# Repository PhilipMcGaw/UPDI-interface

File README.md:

# UPDI-interface

This is a KiCad PCB that breaks out a common USB‑to‑TTL serial adapter (often sold as a “USB to TTL Serial Communication Conversion Module”) into UPDI, UART, and RS‑485 interfaces. The board is meant to sit between your USB adapter and targets such I am using it with my ROV project.

## UART TX/RX swapping (poka‑yoke)

Getting UART TX and RX the wrong way round is easy at design time and painful to fix once the board is built. I have implemented a [poka‑yoke](https://en.wikipedia.org/wiki/Poka-yoke) crossover: two solder bridges  let you route either straight‑through or swapped connections by changing which pads are bridged—no trace cuts or bodge wires. How it works and how to use it in other projects: [UART TX/RX swapping made simple](https://philipmcgaw.com/uart-tx-rx-swapping-made-simple/).

## License

 * Hardware design files in this repository are licensed under the **[CERN Open Hardware Licence v2 — Strongly Reciprocal (CERN-OHL-S-2.0)](https://gitlab.com/ohwr/project/cernohl/-/wikis/uploads/819d71bea3458f71fba6cf4fb0f2de6b/cern_ohl_s_v2.txt)**, an open source hardware license recommended by the [Open Source Hardware Association (OSHWA)](https://oshwa.org/).
 * Software files in this repository are licensed under the **[Creatice Commons - Attribution-NonCommercial-ShareAlike 4.0 International (CC BY-NC-SA 4.0)](https://creativecommons.org/licenses/by-nc-sa/4.0/)**

- **Copyright:** [Philip McGaw](https://philipmcgaw.com/)

You may use, study, modify, and redistribute the sorcecode, schematic and PCB layout under those terms. **Derivative designs must be released under the same license(s).** If you share the design or boards built from it, include a link to the licenses.

## Related links

- [SquashedFly](https://squashedfly.eu/)
- [UART TX/RX swapping made simple](https://philipmcgaw.com/uart-tx-rx-swapping-made-simple/) — poka‑yoke UART symbol and footprints used on this board
- [KiCad](https://www.kicad.org/) — PCB design software

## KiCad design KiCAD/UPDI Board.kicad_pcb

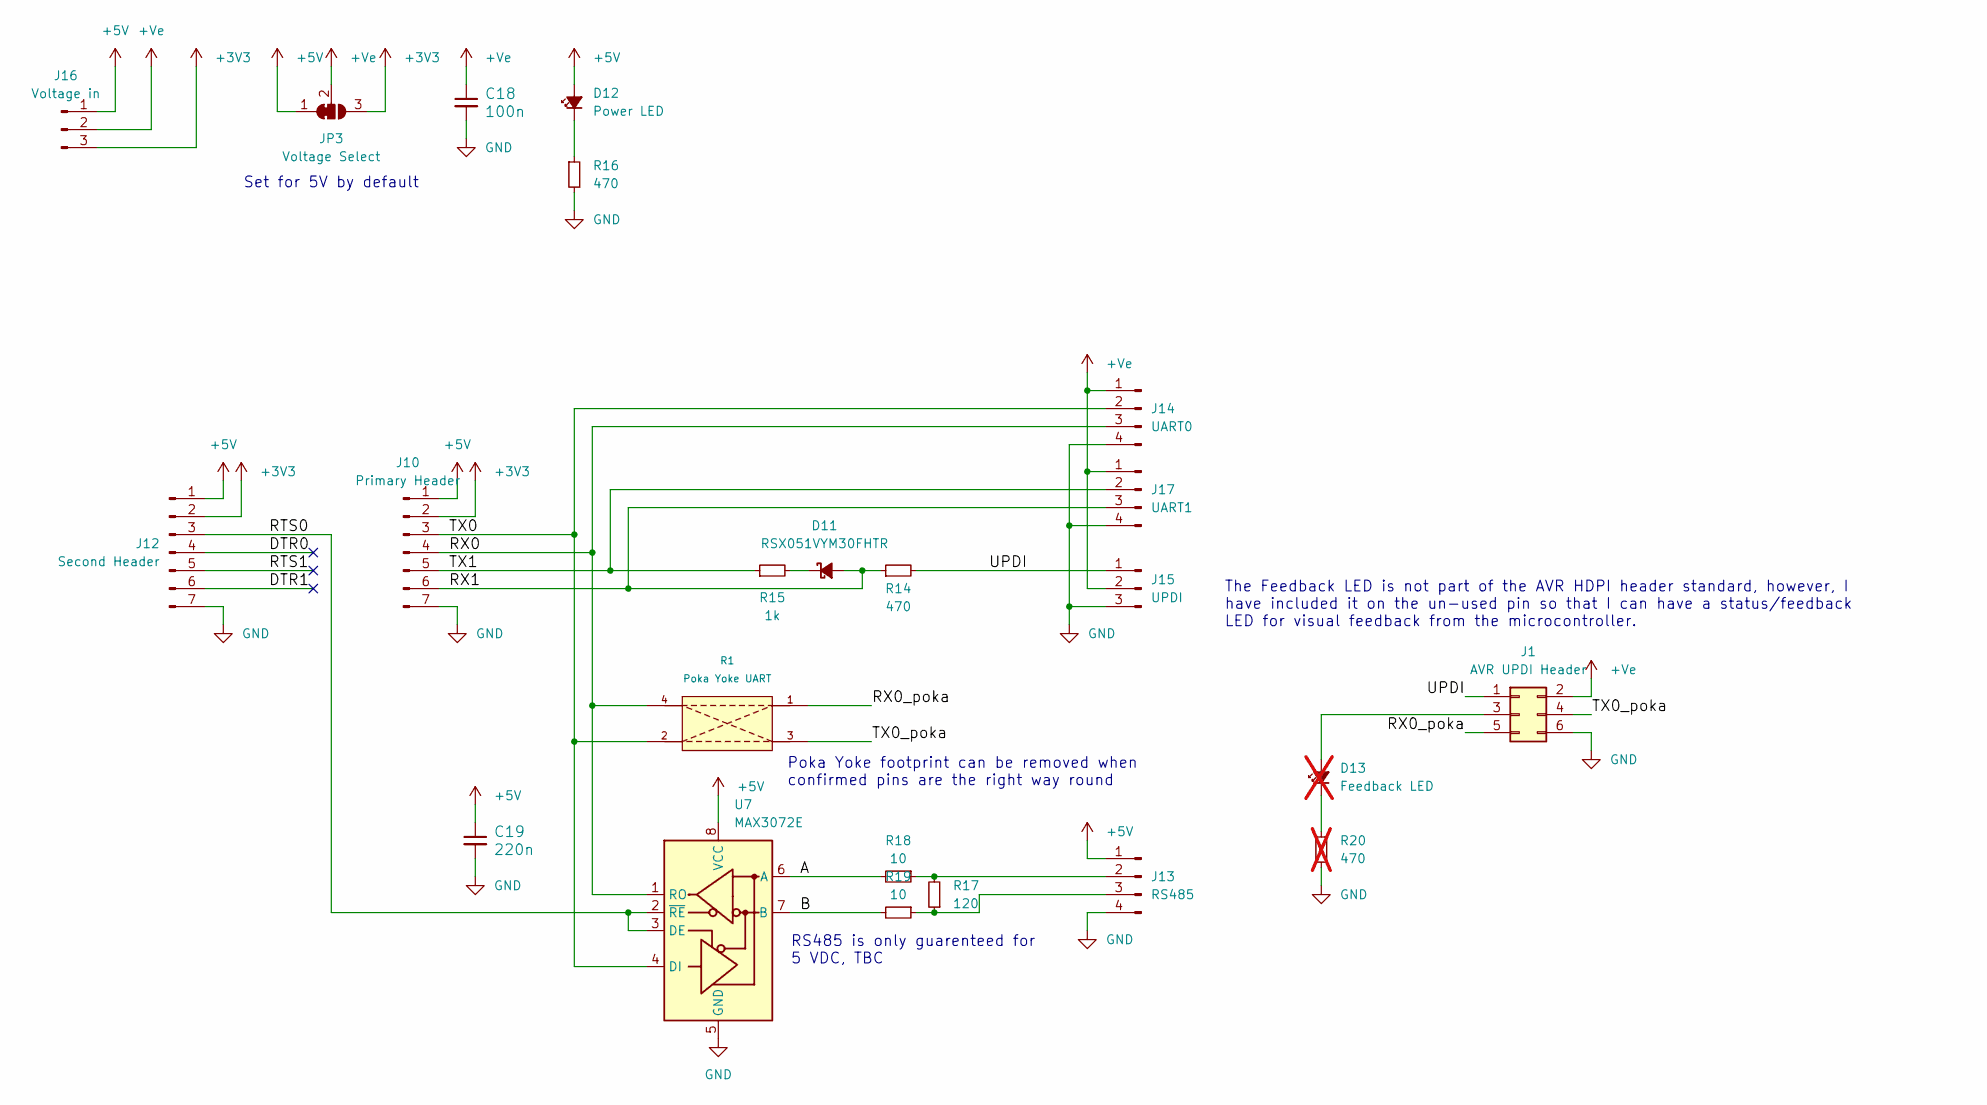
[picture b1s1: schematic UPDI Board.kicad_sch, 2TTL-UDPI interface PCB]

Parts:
C18: 100n; C_0805_2012Metric_Pad1.18x1.45mm_HandSolder
C19: 220n; C_0805_2012Metric_Pad1.18x1.45mm_HandSolder
D11: RSX051VYM30FHTR; D_SOD-323_HandSoldering
D12: Power LED; LED_0805_2012Metric_Pad1.15x1.40mm_HandSolder
D13: Feedback LED; LED_0805_2012Metric_Pad1.15x1.40mm_HandSolder; not fitted
J1: AVR UPDI Header; PinHeader_2x03_P2.54mm_Vertical
J10: Primary Header; PinSocket_1x07_P2.54mm_Vertical
J12: Second Header; PinSocket_1x07_P2.54mm_Vertical
J13: RS485; PinHeader_1x04_P2.54mm_Vertical
J14: UART0; PinHeader_1x04_P2.54mm_Vertical
J15: UPDI; PinHeader_1x03_P2.54mm_Vertical
J16: Voltage in; PinSocket_1x03_P2.54mm_Vertical
J17: UART1; PinHeader_1x04_P2.54mm_Vertical
JP3: Voltage Select; SolderJumper-3_P1.3mm_Bridged12_Pad1.0x1.5mm_NumberLabels
R1: Poka Yoke UART; Poka yoke UART Solder
R14, R16: 470; R_0805_2012Metric_Pad1.20x1.40mm_HandSolder
R15: 1k; R_0805_2012Metric_Pad1.20x1.40mm_HandSolder
R17: 120; R_0805_2012Metric_Pad1.20x1.40mm_HandSolder
R18, R19: 10; R_0805_2012Metric_Pad1.20x1.40mm_HandSolder
R20: 470; R_0805_2012Metric_Pad1.20x1.40mm_HandSolder; not fitted
U7: MAX3072E; SOIC-8_3.9x4.9mm_P1.27mm

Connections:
+3V3: J10.2, J12.2, J16.3, JP3.3 (B)
+5V: C19.1, D12.2 (A), J10.1, J12.1, J13.1, J16.1, JP3.1 (A), U7.8 (VCC)
+Ve: C18.1, J1.2, J14.1, J15.2, J16.2, J17.1, JP3.2 (C)
/A: R18.2, U7.6 (A)
/B: R19.2, U7.7 (B)
/DTR0: J12.4
/DTR1: J12.6
/RTS0: J12.3, U7.2 (~RE), U7.3 (DE)
/RTS1: J12.5
/RX0: J10.4, J14.3, R1.4, U7.1 (RO)
/RX0_poka: J1.5, R1.1
/RX1: D11.2 (A), J10.6, J17.3, R14.1
/TX0: J10.3, J14.2, R1.2, U7.4 (DI)
/TX0_poka: J1.4, R1.3
/TX1: J10.5, J17.2, R15.1
/UPDI: J1.1, J15.1, R14.2
GND: C18.2, C19.2, J1.6, J10.7, J12.7, J13.4, J14.4, J15.3, J17.4, R16.2, R20.2, U7.5 (GND)
unnamed: D11.1 (K), R15.2
unnamed: D12.1 (K), R16.1
unnamed: D13.2 (A), J1.3
unnamed: D13.1 (K), R20.1
unnamed: J13.2, R17.2, R18.1
unnamed: J13.3, R17.1, R19.1

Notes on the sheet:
Poka Yoke footprint can be removed when confirmed pins are the right way round
Set for 5V by default
RS485 is only guarenteed for 5 VDC, TBC
The Feedback LED is not part of the AVR HDPI header standard, however, I have included it on the un-used pin so that I can have a status/feedback LED for visual feedback from the microcontroller.

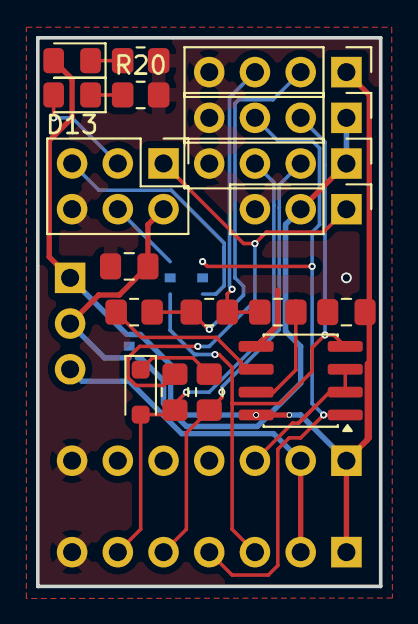
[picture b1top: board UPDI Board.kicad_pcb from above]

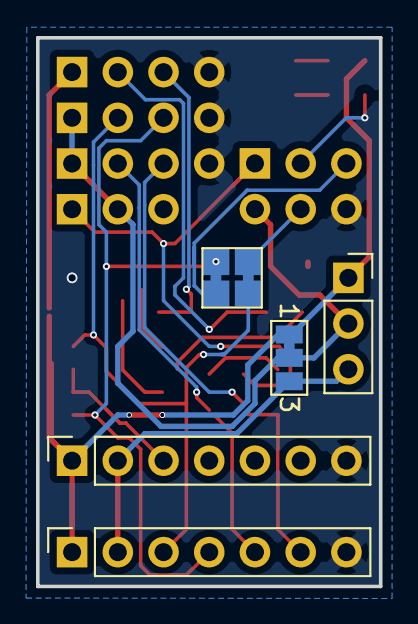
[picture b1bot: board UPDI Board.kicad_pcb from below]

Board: 2 copper layers, 19.1 x 30.5 mm, 23 parts (5 on the bottom side), 20 nets.

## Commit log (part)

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2026-05-26 Uploaded the design files
2026-05-26 added ground plane
2026-06-10 Modified linguist attributes

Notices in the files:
README.md:
License: CC BY-NC-SA
Hardware: CERN-OHL-S
